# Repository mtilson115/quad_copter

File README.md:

quad_copter
===========

Microchip PIC32MX795F512L With uCOS RTOS and Accel Gyro driver port from arduino

**Compiling**

1. Install the xc32 compiler from microchip
2. Modify Makefile to point CC to the to where the compiler is located
3. type make

**Output Files**

A binary (same as a .elf) and a .hex file will be placed in the BIN directory

**Modifying what is included in the build**

In side Makefile, you can modify the DIRS variable to include new folders to compile.

**Required directory structure**

If you do add new folders to the build, you must use the ./src and ./inc file naming structure for the
build system to work.

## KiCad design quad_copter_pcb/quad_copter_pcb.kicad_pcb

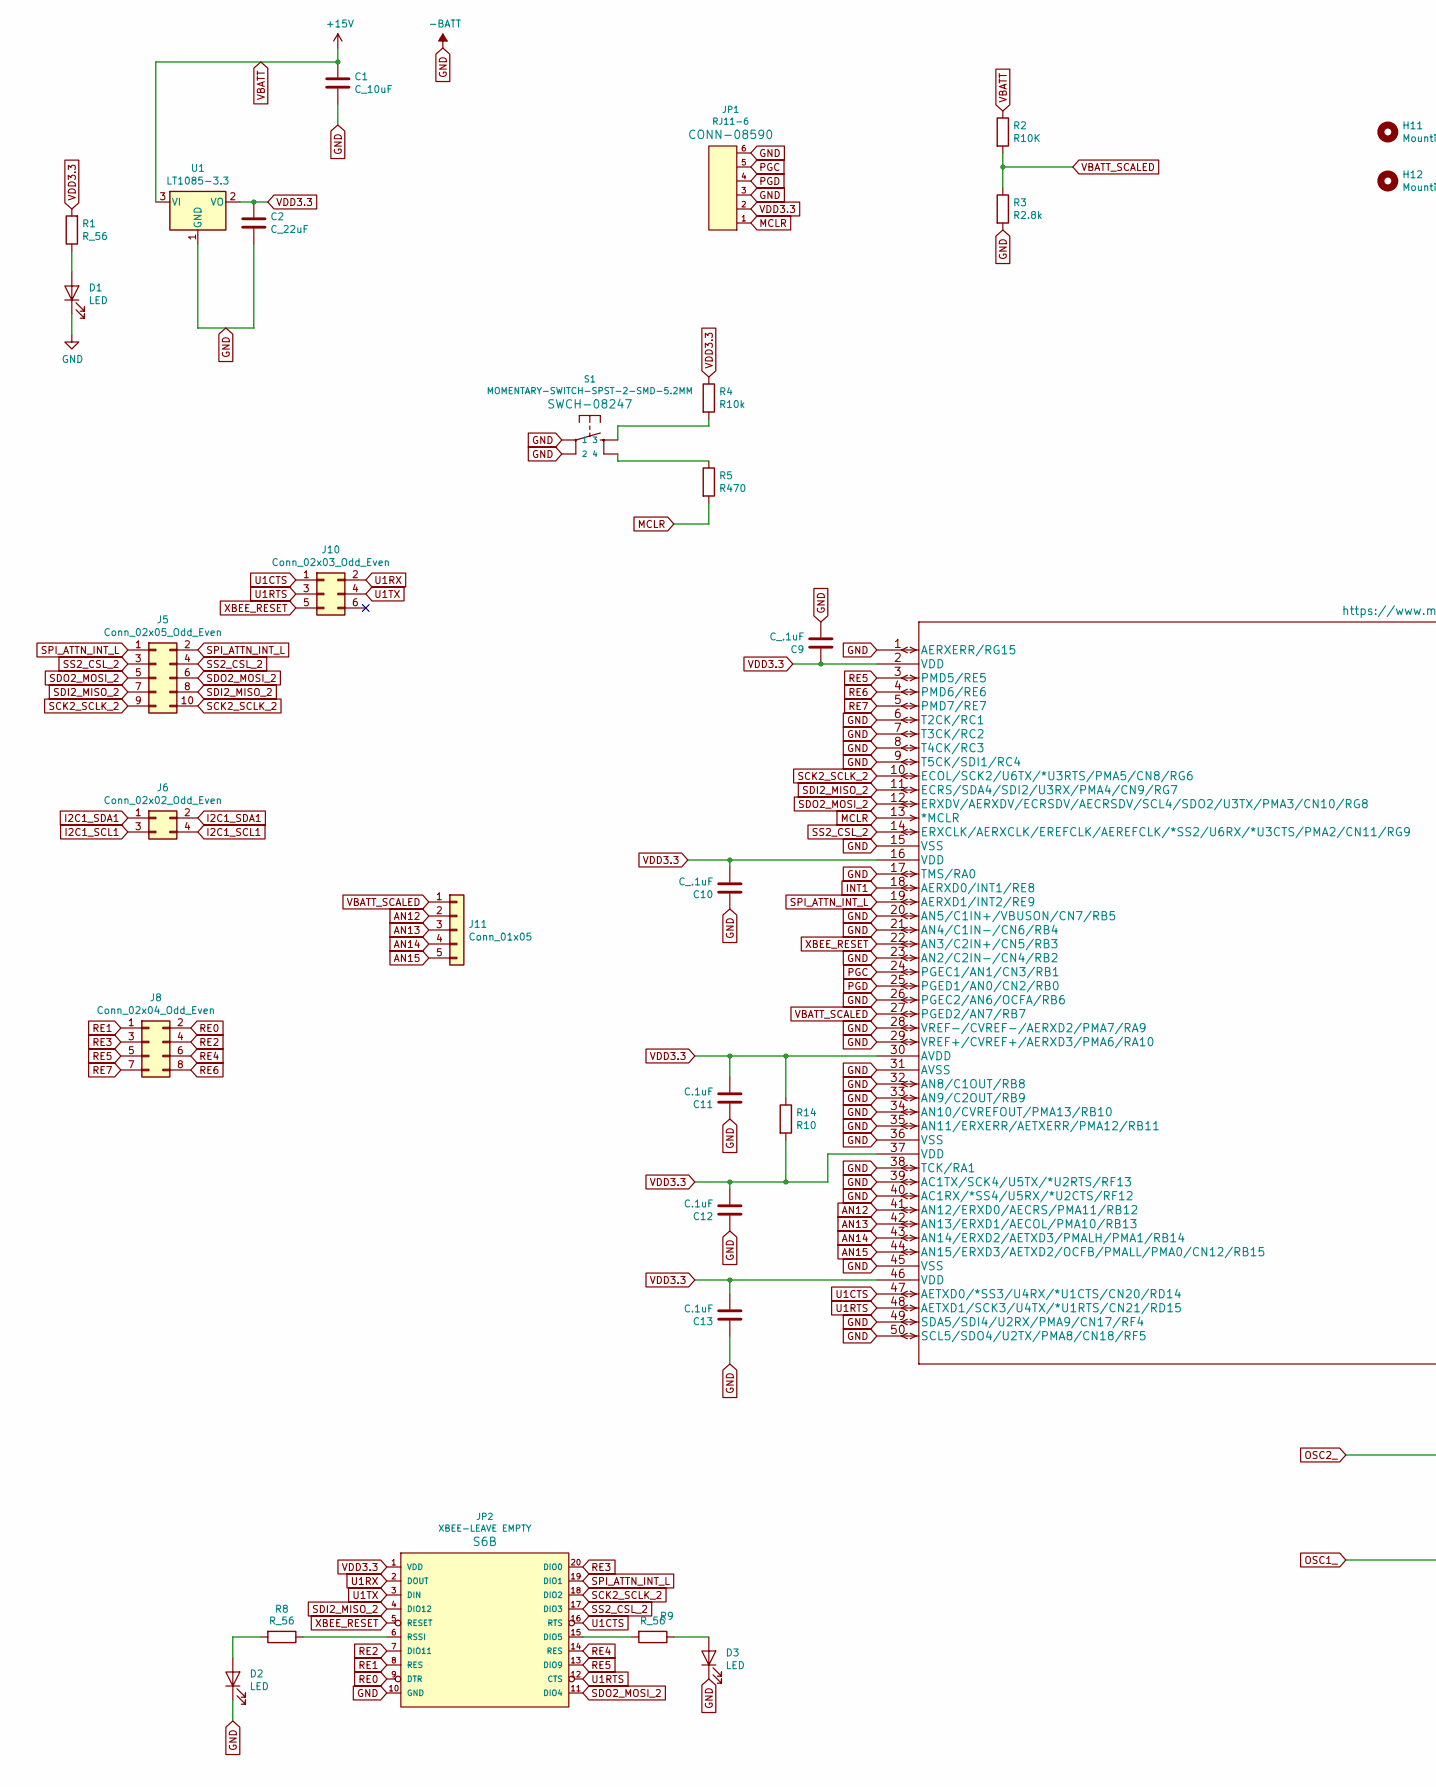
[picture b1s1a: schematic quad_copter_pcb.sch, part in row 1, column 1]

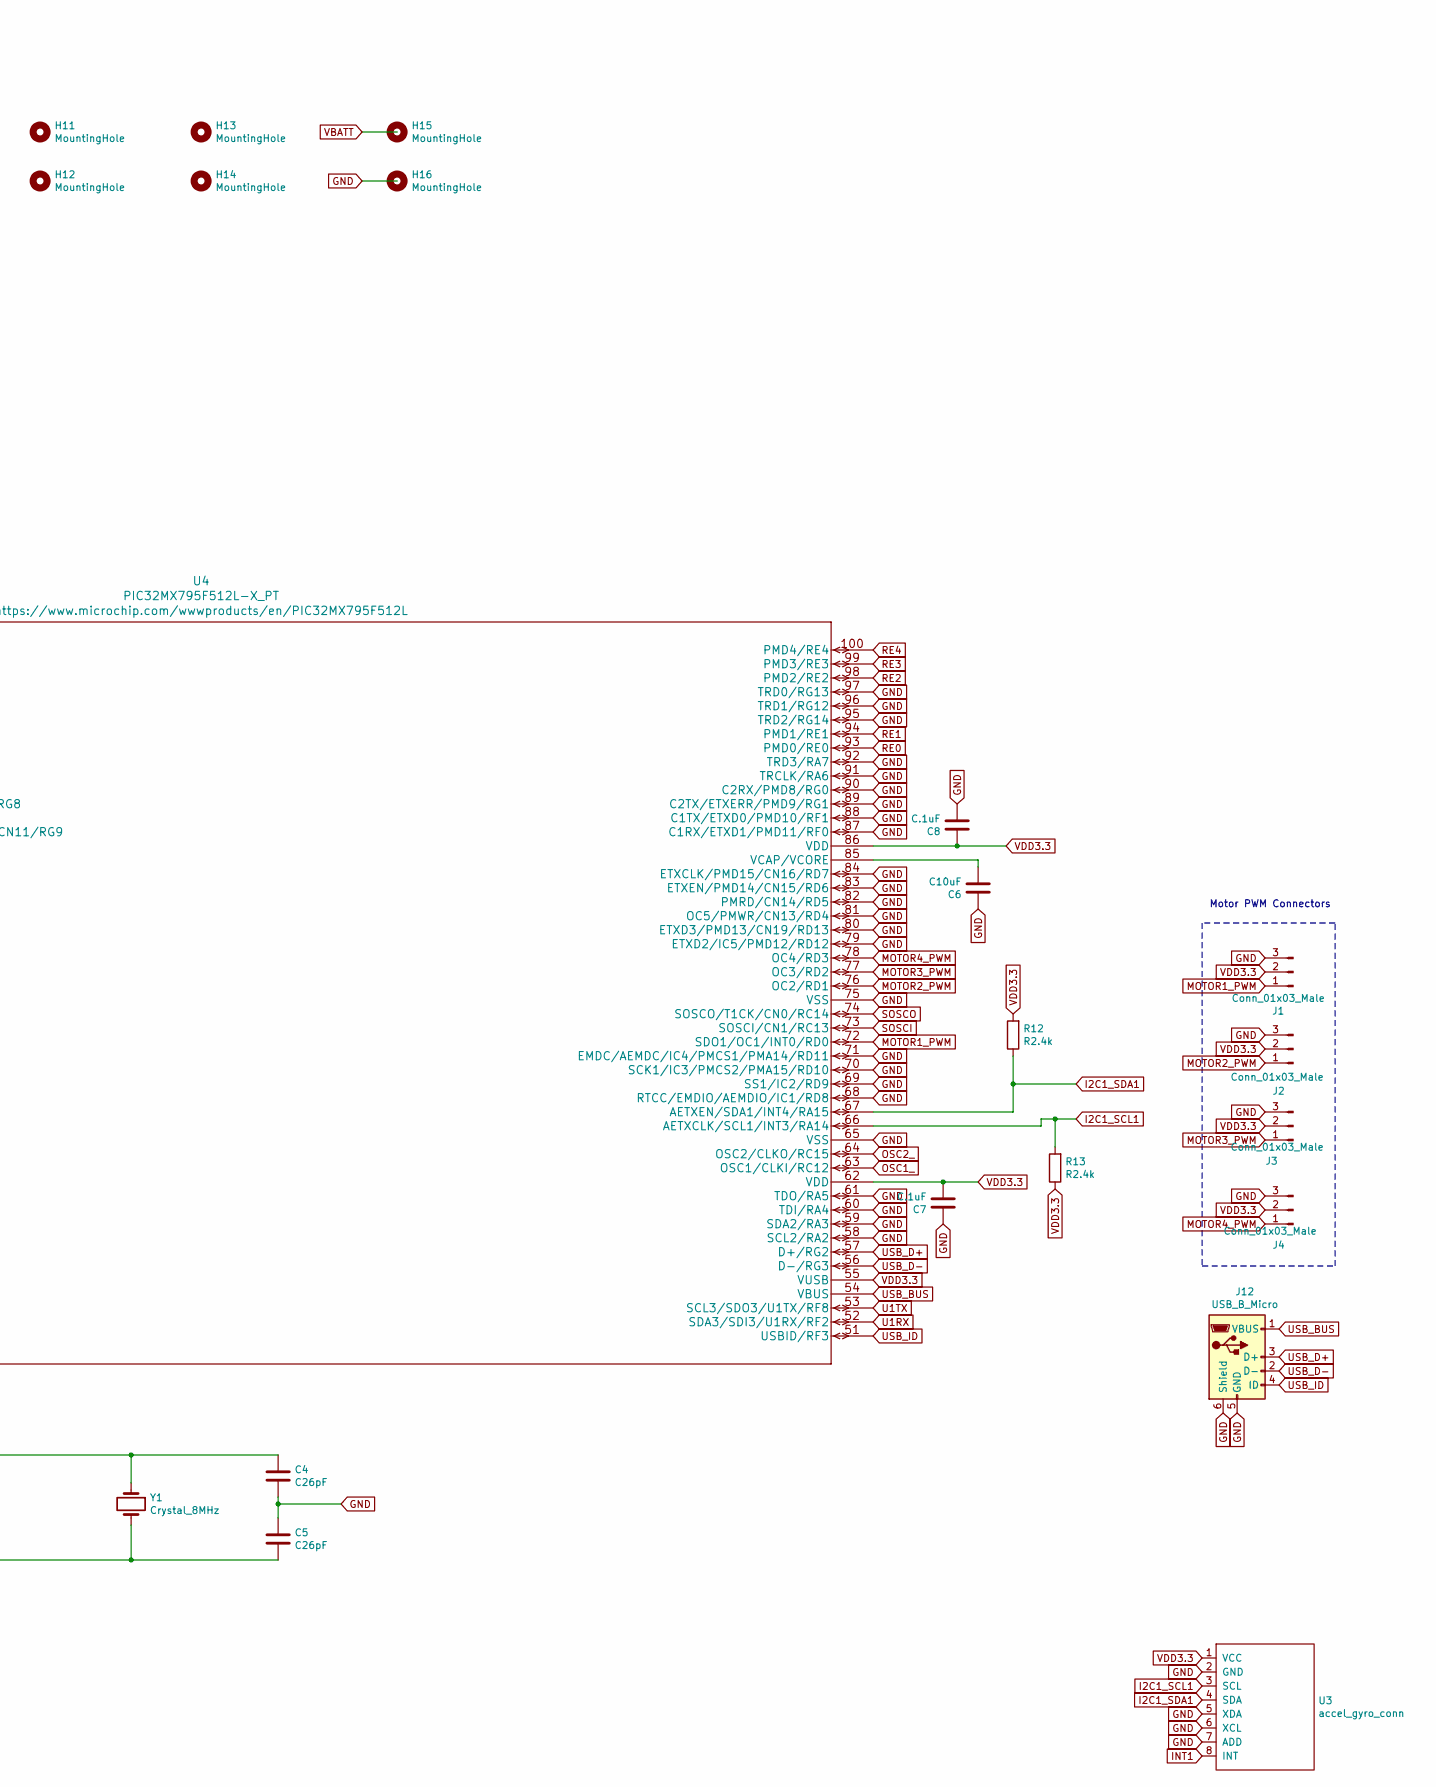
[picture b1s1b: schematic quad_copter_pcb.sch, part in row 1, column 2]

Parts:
C1: C_10uF; C_0805_2012Metric_Pad1.15x1.40mm_HandSolder
C2: C_22uF; C_1206_3216Metric_Pad1.42x1.75mm_HandSolder
C4, C5: C26pF; C_0603_1608Metric_Pad1.05x0.95mm_HandSolder
C6: C10uF; C_0603_1608Metric_Pad1.05x0.95mm_HandSolder
C7, C8, C11, C12, C13: C.1uF; C_0603_1608Metric_Pad1.05x0.95mm_HandSolder
C9, C10: C_.1uF; C_0603_1608Metric_Pad1.05x0.95mm_HandSolder
D1, D2, D3: LED; LED_1206_3216Metric_Pad1.42x1.75mm_HandSolder
H11, H12, H13, H14, H15, H16: MountingHole; MountingHole_3.2mm_M3
J1, J2, J3, J4: Conn_01x03_Male; PinHeader_1x03_P2.54mm_Vertical
J5: Conn_02x05_Odd_Even; PinHeader_2x05_P2.54mm_Vertical
J6: Conn_02x02_Odd_Even; PinHeader_2x02_P2.54mm_Vertical
J8: Conn_02x04_Odd_Even; PinHeader_2x04_P2.54mm_Vertical
J10: Conn_02x03_Odd_Even; PinHeader_2x03_P2.54mm_Vertical
J11: Conn_01x05; PinHeader_1x05_P2.54mm_Vertical
J12: USB_B_Micro; USB_Micro-B_Amphenol_10103594-0001LF_Horizontal
JP1: RJ11-6
JP2: XBEE-LEAVE EMPTY; XBEE
R1, R8, R9: R_56; R_0805_2012Metric_Pad1.15x1.40mm_HandSolder
R2: R10K; R_0805_2012Metric_Pad1.15x1.40mm_HandSolder
R3: R2.8k; R_0805_2012Metric_Pad1.15x1.40mm_HandSolder
R4: R10k; R_0805_2012Metric_Pad1.15x1.40mm_HandSolder
R5: R470; R_0603_1608Metric_Pad1.05x0.95mm_HandSolder
R12, R13: R2.4k; R_0805_2012Metric_Pad1.15x1.40mm_HandSolder
R14: R10; R_0805_2012Metric_Pad1.15x1.40mm_HandSolder
S1: MOMENTARY-SWITCH-SPST-2-SMD-5.2MM; TACTILE_SWITCH_SMD_5.2MM
U1: LT1085-3.3; TO-263-3_TabPin2
U3: accel_gyro_conn; PinSocket_1x08_P2.54mm_Vertical
U4: PIC32MX795F512L-X_PT; TQFP-100_12x12mm_P0.4mm
Y1: Crystal_8MHz; HC49UP

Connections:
AN12: J11.2, U4.41 (AN12/ERXD0/AECRS/PMA11/RB12)
AN13: J11.3, U4.42 (AN13/ERXD1/AECOL/PMA10/RB13)
AN14: J11.4, U4.43 (AN14/ERXD2/AETXD3/PMALH/PMA1/RB14)
AN15: J11.5, U4.44 (AN15/ERXD3/AETXD2/OCFB/PMALL/PMA0/CN12/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)
GND: C1.2, C2.2, C4.2, C5.1, C6.1, C7.1, C8.2, C9.2, C10.1, C11.1, C12.1, C13.1, D1.1 (K), D2.1 (K), D3.1 (K), J1.3, J2.3, J3.3, J4.3, J12.5 (GND), J12.6 (Shield), JP1.3, JP1.6, JP2.10 (GND), R3.2, S1.1, S1.2, U1.1 (GND), U3.2 (GND), U3.5 (XDA), U3.6 (XCL), U3.7 (ADD), U4.1 (AERXERR/RG15), U4.6 (T2CK/RC1), U4.7 (T3CK/RC2), U4.8 (T4CK/RC3), U4.9 (T5CK/SDI1/RC4), U4.15 (VSS), U4.17 (TMS/RA0), U4.20 (AN5/C1IN+/VBUSON/CN7/RB5), U4.21 (AN4/C1IN-/CN6/RB4), U4.23 (AN2/C2IN-/CN4/RB2), U4.26 (PGEC2/AN6/OCFA/RB6), U4.28 (VREF-/CVREF-/AERXD2/PMA7/RA9), U4.29 (VREF+/CVREF+/AERXD3/PMA6/RA10), U4.31 (AVSS), U4.32 (AN8/C1OUT/RB8), U4.33 (AN9/C2OUT/RB9), U4.34 (AN10/CVREFOUT/PMA13/RB10), U4.35 (AN11/ERXERR/AETXERR/PMA12/RB11), U4.36 (VSS), U4.38 (TCK/RA1), U4.39 (AC1TX/SCK4/U5TX/*U2RTS/RF13), U4.40 (AC1RX/*SS4/U5RX/*U2CTS/RF12), U4.45 (VSS), U4.49 (SDA5/SDI4/U2RX/PMA9/CN17/RF4), U4.50 (SCL5/SDO4/U2TX/PMA8/CN18/RF5), U4.58 (SCL2/RA2), U4.59 (SDA2/RA3), U4.60 (TDI/RA4), U4.61 (TDO/RA5), U4.65 (VSS), U4.68 (RTCC/EMDIO/AEMDIO/IC1/RD8), U4.69 (SS1/IC2/RD9), U4.70 (SCK1/IC3/PMCS2/PMA15/RD10), U4.71 (EMDC/AEMDC/IC4/PMCS1/PMA14/RD11), U4.75 (VSS), U4.79 (ETXD2/IC5/PMD12/RD12), U4.80 (ETXD3/PMD13/CN19/RD13), U4.81 (OC5/PMWR/CN13/RD4), U4.82 (PMRD/CN14/RD5), U4.83 (ETXEN/PMD14/CN15/RD6), U4.84 (ETXCLK/PMD15/CN16/RD7), U4.87 (C1RX/ETXD1/PMD11/RF0), U4.88 (C1TX/ETXD0/PMD10/RF1), U4.89 (C2TX/ETXERR/PMD9/RG1), U4.90 (C2RX/PMD8/RG0), U4.91 (TRCLK/RA6), U4.92 (TRD3/RA7), U4.95 (TRD2/RG14), U4.96 (TRD1/RG12), U4.97 (TRD0/RG13)
I2C1_SCL1: J6.3, J6.4, R13.2, U3.3 (SCL), U4.66 (AETXCLK/SCL1/INT3/RA14)
I2C1_SDA1: J6.1, J6.2, R12.1, U3.4 (SDA), U4.67 (AETXEN/SDA1/INT4/RA15)
INT1: U3.8 (INT), U4.18 (AERXD0/INT1/RE8)
MCLR: JP1.1, R5.2, U4.13 (*MCLR)
MOTOR1_PWM: J1.1, U4.72 (SDO1/OC1/INT0/RD0)
MOTOR2_PWM: J2.1, U4.76 (OC2/RD1)
MOTOR3_PWM: J3.1, U4.77 (OC3/RD2)
MOTOR4_PWM: J4.1, U4.78 (OC4/RD3)
unnamed: C6.2, U4.85 (VCAP/VCORE)
unnamed: D1.2 (A), R1.1
unnamed: D2.2 (A), R8.2
unnamed: D3.2 (A), R9.1
unnamed: JP2.6 (RSSI), R8.1
unnamed: JP2.15 (DIO5), R9.2
unnamed: R4.2, S1.3
unnamed: R5.1, S1.4
OSC1_: C5.2, U4.63 (OSC1/CLKI/RC12), Y1.2
OSC2_: C4.1, U4.64 (OSC2/CLKO/RC15), Y1.1
PGC: JP1.5, U4.24 (PGEC1/AN1/CN3/RB1)
PGD: JP1.4, U4.25 (PGED1/AN0/CN2/RB0)
RE0: J8.2, JP2.9 (DTR), U4.93 (PMD0/RE0)
RE1: J8.1, JP2.8 (RES), U4.94 (PMD1/RE1)
RE2: J8.4, JP2.7 (DIO11), U4.98 (PMD2/RE2)
RE3: J8.3, JP2.20 (DIO0), U4.99 (PMD3/RE3)
RE4: J8.6, JP2.14 (RES), U4.100 (PMD4/RE4)
RE5: J8.5, JP2.13 (DIO9), U4.3 (PMD5/RE5)
RE6: J8.8, U4.4 (PMD6/RE6)
RE7: J8.7, U4.5 (PMD7/RE7)
SCK2_SCLK_2: J5.9, J5.10, JP2.18 (DIO2), U4.10 (ECOL/SCK2/U6TX/*U3RTS/PMA5/CN8/RG6)
SDI2_MISO_2: J5.7, J5.8, JP2.4 (DIO12), U4.11 (ECRS/SDA4/SDI2/U3RX/PMA4/CN9/RG7)
SDO2_MOSI_2: J5.5, J5.6, JP2.11 (DIO4), U4.12 (ERXDV/AERXDV/ECRSDV/AECRSDV/SCL4/SDO2/U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)
SOSCI: U4.73 (SOSCI/CN1/RC13)
SOSCO: U4.74 (SOSCO/T1CK/CN0/RC14)
SPI_ATTN_INT_L: J5.1, J5.2, JP2.19 (DIO1), U4.19 (AERXD1/INT2/RE9)
SS2_CSL_2: J5.3, J5.4, JP2.17 (DIO3), U4.14 (ERXCLK/AERXCLK/EREFCLK/AEREFCLK/*SS2/U6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)
U1CTS: J10.1, JP2.16 (RTS), U4.47 (AETXD0/*SS3/U4RX/*U1CTS/CN20/RD14)
U1RTS: J10.3, JP2.12 (CTS), U4.48 (AETXD1/SCK3/U4TX/*U1RTS/CN21/RD15)
U1RX: J10.2, JP2.2 (DOUT), U4.52 (SDA3/SDI3/U1RX/RF2)
U1TX: J10.4, JP2.3 (DIN), U4.53 (SCL3/SDO3/U1TX/RF8)
USB_BUS: J12.1 (VBUS), U4.54 (VBUS)
USB_D+: J12.3 (D+), U4.57 (D+/RG2)
USB_D-: J12.2 (D-), U4.56 (D-/RG3)
USB_ID: J12.4 (ID), U4.51 (USBID/RF3)
VBATT: C1.1, R2.1, U1.3 (VI)
VBATT_SCALED: J11.1, R2.2, R3.1, U4.27 (PGED2/AN7/RB7)
VDD3.3: C2.1, C7.2, C8.1, C9.1, C10.2, C11.2, C12.2, C13.2, J1.2, J2.2, J3.2, J4.2, JP1.2, JP2.1 (VDD), R1.2, R4.1, R12.2, R13.1, R14.1, R14.2, U1.2 (VO), U3.1 (VCC), U4.2 (VDD), U4.16 (VDD), U4.30 (AVDD), U4.37 (VDD), U4.46 (VDD), U4.55 (VUSB), U4.62 (VDD), U4.86 (VDD)
XBEE_RESET: J10.5, JP2.5 (RESET), U4.22 (AN3/C2IN+/CN5/RB3)

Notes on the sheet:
Motor PWM Connectors

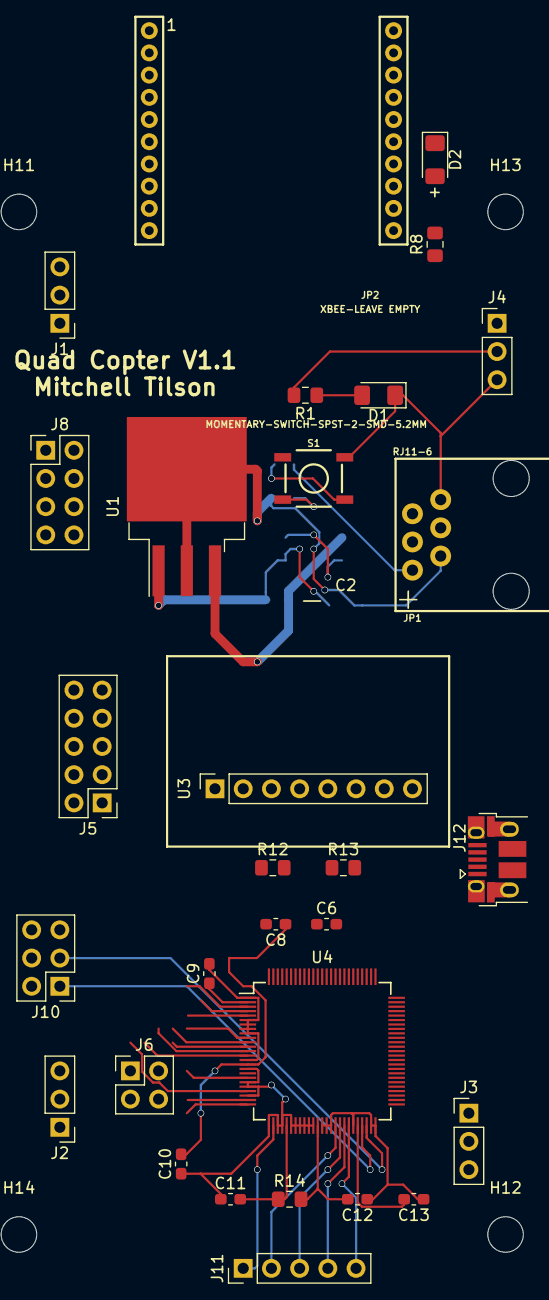
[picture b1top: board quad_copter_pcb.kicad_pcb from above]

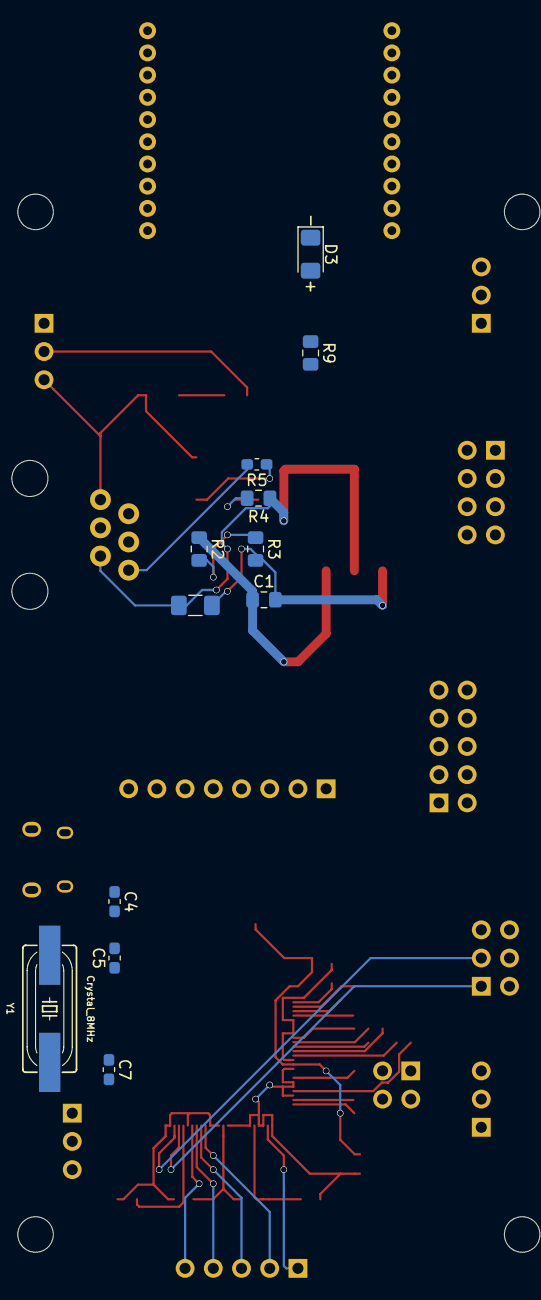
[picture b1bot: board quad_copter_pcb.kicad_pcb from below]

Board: 2 copper layers, 46 parts (12 on the bottom side), 50 nets.

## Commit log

2014-09-03 Update call to Uart_write to not pass 'TRUE' or 'FALSE'. All writes are blocking for now.
2014-09-03 Update to README for clarification of compiler (MPLABX on Linux).
2014-10-25 Remove make file because it is system dependant
2014-10-25 Adding git ignore file
2014-10-25 Update .gitignore for object files
2014-10-25 Removing Ojbect files from git repo and updating .gitignore to not include them
2014-10-25 Remove tags files because they are uncessary
2014-10-25 Remove nbproject files
2014-10-25 More ignore files and folders
2014-10-25 Remove dist folder
2014-10-25 Updates to make it compile
2014-10-27 Update to compilable version
2014-10-28 Remove system specific data
2014-10-28 Remove useless files
2014-10-28 Remove extra call to start_reader
2014-10-28 Update to remove unnecessary call
2016-01-23 Build system fixed. This will now build without the use of the MPLAB IDE
2016-01-23 Update the README
2016-01-23 Added the make file back in and removed it from .gitignore. The main project will now compile for linux
2016-01-25 Update the Makefile to generate a map file and start printing the accel device ID
2016-01-25 Start of the pwm drivers
2016-01-25 Fix tabs
2016-01-25 Update .gitignore for tags-he
2016-01-25 Update the PWM drivers to have start and stop functionality
2016-01-26 PWM updates to allow duty cycle changes on the fly and some test code in button reader
2016-01-31 Remove white space
2016-01-31 Remove whitespace
2016-02-09 Update to use 256 as the PWM pre-scale value
2016-02-15 Check to ensure PWM is initialized prior to make any changes and fix some whie space stuff
2016-02-16 Fixed comments in PWM driver and added the start of the SPI driver
2016-02-17 Changes to get SPI driver compiling for now
2016-03-07 Updates for spi interupts
2016-03-07 Fix interrupt flag register
2016-03-07 Fix interrupt flag register for real this time
2016-03-07 Remove whitspace
2016-03-07 Ignore *.swp files
2016-03-07 Updates for gitignore and new binary folder
2016-03-07 Change where the compiler is located for my mac
2016-03-07 More interrupt fixes
2018-11-20 Fix whitespace and typo
2018-11-21 Playing around with the ESC.
2018-11-23 Testing the accel gyro again and adding the python plotting utility for the accel gyro
2018-11-23 Update the live accel plotter to be faster
2018-11-24 Fixing some printf issues and attempting to run at a higher rate
2018-11-24 Fix comment in make file
2018-11-24 Fix comment in Makefile
2018-11-25 Initial PCB
2018-12-10 Add the PCB
2018-12-10 Few more PCB files
2018-12-21 PCB changes
2018-12-23 Functioning with Quad Copter V1.0
2018-12-23 The start of cleaning up the accel gyro code (MPU6050)
2018-12-24 Does not build!
2018-12-29 DMP code is ugly but builds
2019-01-01 Start of clean up
2019-01-01 Remove unused includes in app.cpp
2019-01-01 Start adding HAL
2019-01-07 Update the schematic stuffs
2019-01-07 small changes for SPI and Xbee
2019-01-08 remove .swp file
2019-01-08 Doesn't build: Added xbee init code
2019-01-08 Comments and cleanup
2019-01-13 Remove unused file
2019-01-15 Xbee test code
2019-01-19 One step closer to an xbee comm layer (added a semaphore call back structure)
2019-01-19 Testing with semaphores. Seems to be working :-)
2019-01-21 Comms layer can now read the status from the xbee and parse it
2019-01-22 Working xbee comms layer
2019-01-22 Printf now uses comms_xbee layer
2019-01-26 The real change was to update the stack size for the test app because it was using the accel libs
2019-01-27 Everything works again
2019-01-27 Try to enable interrupts for the MPU6050 (accel_gyro)
2019-01-28 Currently runs but dies after a bit. Probably a buffer overrun.
2019-01-28 Unfinished reading of RX during TX
2019-01-29 Ensure RX messages aren't over run as easy during TX and add in logic to read messages that are received during a TX message event
2019-01-29 Craps out after a few seconds currently
2019-01-31 Generate a disassembly file (.lst)
2019-01-31 Rando fixes for things
2019-01-31 Upate how the compile flags are set
2019-02-01 Test using snprintf instead
2019-02-01 Fix pull conflict
2019-02-01 Removed accel gyro interrupt. It was too noisy. Polling for now.
2019-02-02 Cleanup and attempting to hand RX during a TX
2019-02-03 Add in the ability to read and parse messages sent while transmitting on the xbee
2019-02-04 Attempting to calculate roll and pitch
2019-02-04 Working on accel algs
2019-02-06 Functioning example for calculating roll and pitch
2019-02-07 Use legacy libc for real and add -fno-short-double (https://www.microchip.com/forums/m988026.aspx)
2019-02-08 Data has to be sent as binary when its floating point for now
2019-02-09 Use OSMem instead of malloc
2019-02-09 Reduce heap size given the OSMem is used
2019-02-09 A few compile time bugs squashed
2019-02-11 Trying to get interrupts working
2019-02-11 Use a single handler for all interrupts
2019-02-12 Enable deferred ISR in the OS. Seems to fix interrupts
2019-02-12 Test and documentation updates
2019-02-12 Clean up
2019-02-13 Add the first step of algorithms
2019-02-13 Something to test! (adds in algorithm, maybe app code, for reading accel and outputing PWM values)
2019-02-14 Update alg_stabilizer to be c++ and fix some compile errors
2019-02-14 Getting closer...
2019-02-16 Broken pwm push
2019-02-17 Update to enable all PWMs and rename PWM0 to PWM1 just to fit the motor names
2019-02-17 Small fix
2019-02-18 It would be driving all 4 motors if I hadn't blown one of them
2019-02-18 Work around for OC3 being broken
2019-02-18 Work around doesn't work, but I think its confusing the Os
2019-02-23 Write an ISR using the compiler format
2019-02-23 Use compiler interrupts and use single compare continuous toggle and interrupts for TMR2 and OC3
2019-03-02 Minor chagnes to use RE1 instead of RE6 for the broken PWM
2019-03-02 Use objects for the BSP level motor control
2019-03-02 Start to setup for RX message handling. Next step is to use it for changing the motor speed
2019-03-03 First iteration on actually calculating motor speeds
2019-04-14 Enhancements for communication and fixes for the serial buffer reader
2019-04-19 Add filter and change messages. This will need to be merged with what is at home
2019-04-20 Stabilizer updates
2019-04-24 Preparing for first flight
2019-04-24 Start throttle at zero
2019-04-25 Increase P and I constants for the controller. Last time it didn't respond fast enough and we rolled
2019-04-25 Create a more flexible developement setup for setting the PI and I constants and clean up the code a little
2019-04-25 Updating testing python scripts to be threaded
2019-04-26 Just a push
2019-04-27 Set fail safe for the throttle and update the test script
2019-04-27 Fix compile time error
2019-04-27 Change the script for the desktop
2019-04-27 Fixes
2019-04-27 Set serial for laptop
2019-04-27 Constant update and better fail safe
2019-05-29 Minor changes
2019-05-29 Only send debug data when compiled for it
2019-06-02 Add battery voltage tracking.
2019-06-03 Test script modification
2019-06-08 Add flash write functionality
2019-06-10 Compiling on my mac :-) :-)
2019-06-10 Update gitignore for mac files
2019-06-10 Python test code update for new serial port
2019-06-12 Make file changes to get more information from the link step
2019-06-13 Add a custom linker script
2019-06-17 One step closer to having a calibration section of flash
2019-06-17 Add in the ability to calibrate the accel gyro on demand and store it in flash
2019-06-18 Add calibration for real
2019-06-20 Closer to having the ability to save calibration to flash
2019-06-21 Saving calibration to flash is now working
2019-06-24 Track how how often the accel/gyro produces a sample
2019-06-25 Work around accidentally cutting RE1 too much by using RE6
2019-06-25 Attempt to calibrate the motors
2019-06-26 Throttle cal and filter choice change in MPU6050
2019-06-26 Up the data rate to 200Hz and change how the euler angles are calcualted
2019-06-26 Revert changes to calculations of the angles for now
2019-06-27 Small changes to tune the system
2019-06-27 Make derivative fight changes
2019-07-01 Back on ubuntu and adding some stability updates
2019-07-01 Remove old comment
2019-07-01 Add ability to only flash an image via the make file
2019-07-02 Update file location of flash tool. Flashing via ipe command doesn't work right now
2019-07-02 Compile in debugging output
2019-07-07 Adding debug features
2019-07-07 Add in the ability to set the pitch,roll, and yaw. Yaw not supported by controller yet
2019-07-07 Send battery voltages again
2019-07-07 Make the control task the highest priority
2019-07-08 Whitespace
2019-07-13 Attempting to tune...
2019-07-28 Attempt to handle stack corruption
2020-02-02 PCB updates
2020-02-02 Starting the repairs so that the os can be used again
2020-02-02 More fixing the comms
2020-02-07 Adding files for easy access
2020-03-14 Update alg stabilizer per latest design
2020-03-14 Update the comms code
2020-03-14 Update the drivers
2020-03-14 BSP updates
2020-03-14 Remaning
2020-03-14 Clean up battery reading
2020-03-14 Add some linkage and renaming
2020-03-14 Updates included
2020-03-14 Make sure comms come up first before sending messages
2020-03-15 Small clean up
2020-03-21 Debugging
2020-03-22 Debugging changes
